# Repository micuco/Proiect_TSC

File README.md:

# Proiect_TSC
InkTime este un smartwatch low-cost, open-source, bazat pe microcontroller-ul nRF52840. Proiectul acopera intreg procesul de dezvoltare hardware, de la schema electrica pana la integrarea mecanica intr-o carcasa.

Sistemul este compus din urmatoarele blocuri principale: MCU nRF52840, Power Management (LiPo Charger + DC/DC), IMU, E-paper Display + Driver, Fuel Gauge, USB-C + ESD Protection, Haptic Driver, Butoane, Interfata SWD.

Microcontroller-ul principal gestioneaza: comunicatia BLE, interfata SPI pentru display, I2C pentru senzori (IMU, fuel gauge),USB pentru alimentare si debug.

Sistemul de alimentare include: BQ25180 pentru incarcarea bateriei LiPo, RT6160 pentru conversie DC/DC, multiple condensatoare de decuplare (100nF, 1uF, 4.7uF). Traseele de alimentare sunt dimensionate conform cerintelor (min 0.3mm).

IMU (BMA421): conectat pe I2C (SDA, SCL), semnale de intrerupere: INT1, INT2, utilizat pentru detectarea miscarii si gesturilor.

E-Paper Display: conectare prin SPI (MOSI, SCK, CS, DC, RST), driver dedicat pentru generarea tensiunilor necesare (boost circuit).

Fuel Gauge: monitorizeaza nivelul bateriei, conectat pe I2C, pin ALERT pentru notificari.

Haptic Driver: DRV2605 pentru control vibratii, control prin I2C, semnal enable din MCU.

USB-C: folosit pentru alimentare si comunicatie, protejat cu circuit ESD dedicat.

Butoane: 3 butoane, conectate la GPIO cu rezistente pull-up/pull-down.

Pin Mapping (nRF52840):

| Functie       | Pin     |
| ------------- | ------- |
| I2C SDA       | P0.xx   |
| I2C SCL       | P0.xx   |
| SPI MOSI      | P0.xx   |
| SPI SCK       | P0.xx   |
| EPD CS/DC/RST | GPIO    |
| IMU INT       | GPIO    |
| SWDIO         | dedicat |
| SWDCLK        | dedicat |

Design Decisions: folosirea e-paper pentru consum redus, integrarea fuel gauge pentru autonomie, antena externa pozitionata la marginea PCB-ului, separarea clara a planurilor de masa.

DRC & ERC: verificari efectuate, respectate regulile de routare, fara unghiuri de 90, condensatoare de decuplare aproape de IC-uri.

PCB Design: PCB 2 layer (TOP + BOTTOM), plan de masa pe ambele layere, via stitching pentru GND, componente plasate pe TOP, trasee: power: ≥ 0.3mm, semnal: ≥ 0.15mm, antena: plasata la marginea PCB, fara plan de masa sub ea.

Modelul 3D include: PCB complet cu componente, baterie LiPo (modelata conform datasheet), display e-paper, carcasa smartwatch.

Integrarea presupune: alinierea butoanelor cu carcasa, pozitionarea corecta a USB-C, fixarea bateriei pe test pads, verificarea spatiului intern si a interferentelor..

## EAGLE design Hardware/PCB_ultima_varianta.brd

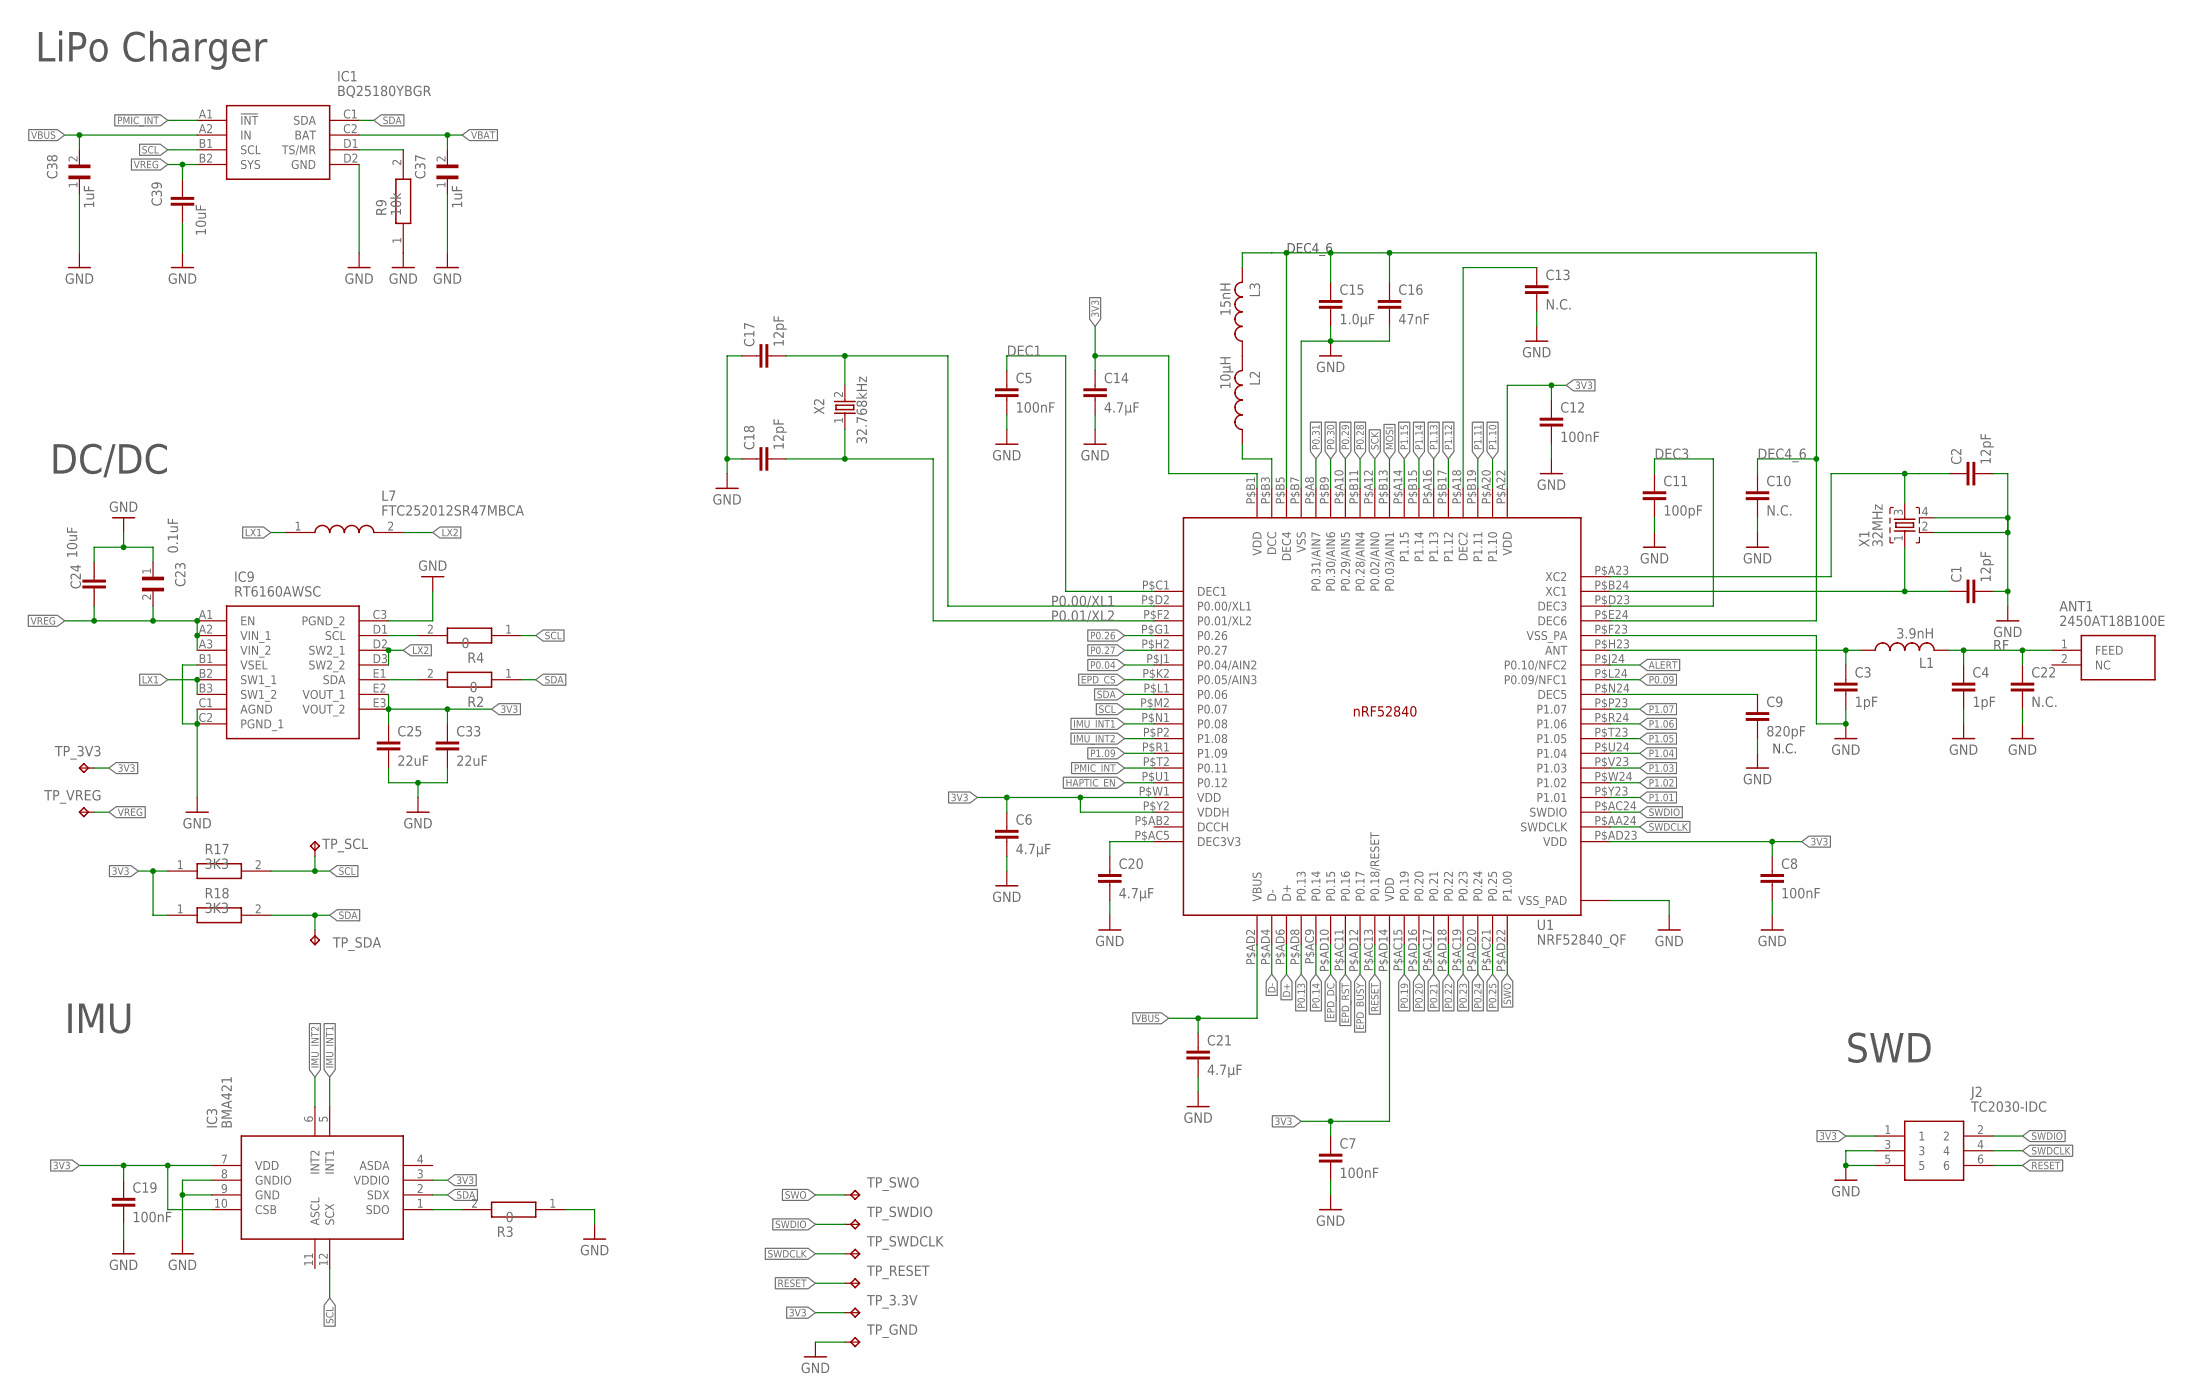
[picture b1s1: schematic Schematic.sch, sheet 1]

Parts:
ANT1: 2450AT18B100E; 2450AT18B100E_ANTC3216X140N
C1, C2, C17, C18: 12pF; NORDIC_NRF_3_RESC0201_L
C3, C4: 1pF; NORDIC_NRF_3_RESC0201_L
C5, C7, C8, C12, C19: 100nF; NORDIC_NRF_3_RESC0201_L
C6, C14, C20, C21: 4.7µF; NORDIC_NRF_3_RESC0201_L
C9: 820pF; NORDIC_NRF_3_RESC0201_L
C10, C13, C22: N.C.; NORDIC_NRF_3_RESC0201_L
C11: 100pF; NORDIC_NRF_3_RESC0201_L
C15: 1.0µF; NORDIC_NRF_3_RESC0201_L
C16: 47nF; NORDIC_NRF_3_RESC0201_L
C23: 0.1uF; GRM011R60J152KE01L_2_CAPC0201X13N
C24, C39: 10uF; NORDIC_NRF_3_RESC0201_L
C25, C33: 22uF; NORDIC_NRF_3_RESC0201_L
C37, C38: 1uF; GRM011R60J152KE01L_2_CAPC0201X13N
IC1: BQ25180YBGR; BQ25180YBGR_BGA8C40P2X4_100X155X50
IC3: BMA421; BMA423_BMA423
IC9: RT6160AWSC; RT6160AWSC_BGA15C40P3X5_140X230X60
J2: TC2030-IDC; TC2030-IDC_TC2030IDC
L1: 3.9nH; NORDIC_NRF_2_RESC0402_L
L2: 10µH; NORDIC_NRF_2_RESC0402_L
L3: 15nH; NORDIC_NRF_2_RESC0402_L
L7: FTC252012SR47MBCA; MLP2016SR47MT0S1_INDC2016X100N
R2, R3, R4: 0; CPF0201D7K68C1_0201
R9: 10k; CPF0201D7K68C1_0201
R17, R18: 3K3; CPF0201D7K68C1_0201
TP_3.3V, TP_3V3: HECTOR_WATCH_1_TPTP20R; HECTOR_WATCH_1_TP20R
TP_GND: HECTOR_WATCH_1_TPTP20R; HECTOR_WATCH_1_TP20R
TP_RESET: HECTOR_WATCH_1_TPTP20R; HECTOR_WATCH_1_TP20R
TP_SCL: HECTOR_WATCH_1_TPTP20R; HECTOR_WATCH_1_TP20R
TP_SDA: HECTOR_WATCH_1_TPTP20R; HECTOR_WATCH_1_TP20R
TP_SWDCLK: HECTOR_WATCH_1_TPTP20R; HECTOR_WATCH_1_TP20R
TP_SWDIO: HECTOR_WATCH_1_TPTP20R; HECTOR_WATCH_1_TP20R
TP_SWO: HECTOR_WATCH_1_TPTP20R; HECTOR_WATCH_1_TP20R
TP_VREG: HECTOR_WATCH_1_TPTP20R; HECTOR_WATCH_1_TP20R
U1: NRF52840_QF; NORDIC_NRF_4_AQFN50P700X700X85_HS-74N
X1: 32MHz; NORDIC_NRF_BT-XTAL_2016_N
X2: 32.768kHz; NORDIC_NRF_1_XTAL_3215_N

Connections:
3V3: C6.1, C7.1, C8.1, C12.1, C14.1, C19.1, C25.1, C33.1, IC3.3 (VDDIO), IC3.7 (VDD), IC3.10 (CSB), IC9.E2 (VOUT_1), IC9.E3 (VOUT_2), J2.1, R17.1, R18.1, TP_3.3V.TP, TP_3V3.TP, U1.P$A22 (VDD), U1.P$AD14 (VDD), U1.P$AD23 (VDD), U1.P$B1 (VDD), U1.P$W1 (VDD), U1.P$Y2 (VDDH); also elsewhere on the board
ALERT: U1.P$J24 (P0.10/NFC2); also elsewhere on the board
D+: U1.P$AD6 (D+); also elsewhere on the board
D-: U1.P$AD4 (D-); also elsewhere on the board
DEC1: C5.1, U1.P$C1 (DEC1)
DEC3: C11.1, U1.P$D23 (DEC3)
DEC4_6: C10.1, C15.1, C16.1, L3.2, U1.P$B5 (DEC4), U1.P$E24 (DEC6)
EPD_BUSY: U1.P$AD12 (P0.17); also elsewhere on the board
EPD_CS: U1.P$K2 (P0.05/AIN3); also elsewhere on the board
EPD_DC: U1.P$AD10 (P0.15); also elsewhere on the board
EPD_RST: U1.P$AC11 (P0.16); also elsewhere on the board
GND: C1.2, C2.2, C3.2, C4.2, C5.2, C6.2, C7.2, C8.2, C9.2, C10.2, C11.2, C12.2, C13.2, C14.2, C15.2, C16.2, C17.1, C18.1, C19.2, C20.2, C21.2, C22.2, C23.1, C24.2, C25.2, C33.2, C37.1, C38.1, C39.2, IC1.D2 (GND), IC3.8 (GNDIO), IC3.9 (GND), IC9.B1 (VSEL), IC9.C1 (AGND), IC9.C2 (PGND_1), IC9.C3 (PGND_2), J2.3, J2.5, R3.1, R9.1, TP_GND.TP, U1.P$74 (VSS_PAD), U1.P$75 (VSS_PAD), U1.P$76 (VSS_PAD), U1.P$77 (VSS_PAD), U1.P$78 (VSS_PAD), U1.P$79 (VSS_PAD), U1.P$80 (VSS_PAD), U1.P$81 (VSS_PAD), U1.P$82 (VSS_PAD), U1.P$83 (VSS_PAD), U1.P$84 (VSS_PAD), U1.P$85 (VSS_PAD), U1.P$86 (VSS_PAD), U1.P$87 (VSS_PAD), U1.P$88 (VSS_PAD), U1.P$89 (VSS_PAD), U1.P$90 (VSS_PAD), U1.P$B7 (VSS), U1.P$F23 (VSS_PA), X1.2, X1.4; also elsewhere on the board
HAPTIC_EN: U1.P$U1 (P0.12); also elsewhere on the board
IMU_INT1: IC3.5 (INT1), U1.P$N1 (P0.08)
IMU_INT2: IC3.6 (INT2), U1.P$P2 (P1.08)
LX1: IC9.B2 (SW1_1), IC9.B3 (SW1_2), L7.1
LX2: IC9.D2 (SW2_1), IC9.D3 (SW2_2), L7.2
MOSI: U1.P$B13 (P0.03/AIN1); also elsewhere on the board
unnamed: IC1.D1 (TS/MR), R9.2
unnamed: IC3.1 (SDO), R3.2
unnamed: C13.1, U1.P$A18 (DEC2)
unnamed: IC9.D1 (SCL), R4.2
unnamed: IC9.E1 (SDA), R2.2
unnamed: C9.1, U1.P$N24 (DEC5)
unnamed: C20.1, U1.P$AC5 (DEC3V3)
unnamed: L2.2, L3.1
unnamed: L2.1, U1.P$B3 (DCC)
unnamed: C3.1, L1.1, U1.P$H23 (ANT)
unnamed: C1.1, U1.P$B24 (XC1), X1.1
unnamed: C2.1, U1.P$A23 (XC2), X1.3
P0.00/XL1: C17.2, U1.P$D2 (P0.00/XL1), X2.2
P0.01/XL2: C18.2, U1.P$F2 (P0.01/XL2), X2.1
P0.04: U1.P$J1 (P0.04/AIN2)
P0.09: U1.P$L24 (P0.09/NFC1)
P0.13: U1.P$AD8 (P0.13); also elsewhere on the board
P0.14: U1.P$AC9 (P0.14); also elsewhere on the board
P0.19: U1.P$AC15 (P0.19)
P0.20: U1.P$AD16 (P0.20)
P0.21: U1.P$AC17 (P0.21)
P0.22: U1.P$AD18 (P0.22)
P0.23: U1.P$AC19 (P0.23)
P0.24: U1.P$AD20 (P0.24)
P0.25: U1.P$AC21 (P0.25)
P0.26: U1.P$G1 (P0.26)
P0.27: U1.P$H2 (P0.27)
P0.28: U1.P$B11 (P0.28/AIN4)
P0.29: U1.P$A10 (P0.29/AIN5)
P0.30: U1.P$B9 (P0.30/AIN6)
P0.31: U1.P$A8 (P0.31/AIN7)
P1.01: U1.P$Y23 (P1.01); also elsewhere on the board
P1.02: U1.P$W24 (P1.02); also elsewhere on the board
P1.03: U1.P$V23 (P1.03)
P1.04: U1.P$U24 (P1.04)
P1.05: U1.P$T23 (P1.05)
P1.06: U1.P$R24 (P1.06)
P1.07: U1.P$P23 (P1.07)
P1.09: U1.P$R1 (P1.09)
P1.10: U1.P$A20 (P1.10)
P1.11: U1.P$B19 (P1.11)
P1.12: U1.P$B17 (P1.12)
P1.13: U1.P$A16 (P1.13)
P1.14: U1.P$B15 (P1.14)
P1.15: U1.P$A14 (P1.15)
PMIC_INT: IC1.A1 (!INT), U1.P$T2 (P0.11)
RESET: J2.6, TP_RESET.TP, U1.P$AC13 (P0.18/RESET)
RF: ANT1.1 (FEED), C4.1, C22.1, L1.2
SCK: U1.P$A12 (P0.02/AIN0); also elsewhere on the board
SCL: IC1.B1 (SCL), IC3.12 (SCX), R4.1, R17.2, TP_SCL.TP, U1.P$M2 (P0.07); also elsewhere on the board
SDA: IC1.C1 (SDA), IC3.2 (SDX), R2.1, R18.2, TP_SDA.TP, U1.P$L1 (P0.06); also elsewhere on the board
SWDCLK: J2.4, TP_SWDCLK.TP, U1.P$AA24 (SWDCLK)
SWDIO: J2.2, TP_SWDIO.TP, U1.P$AC24 (SWDIO)
SWO: TP_SWO.TP, U1.P$AD22 (P1.00)
VBAT: C37.2, IC1.C2 (BAT); also elsewhere on the board
VBUS: C21.1, C38.2, IC1.A2 (IN), U1.P$AD2 (VBUS); also elsewhere on the board
VREG: C23.2, C24.1, C39.1, IC1.B2 (SYS), IC9.A1 (EN), IC9.A2 (VIN_1), IC9.A3 (VIN_2), TP_VREG.TP

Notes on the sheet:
LiPo Charger
DC/DC
IMU
SWD
N.C.
DEC4_6

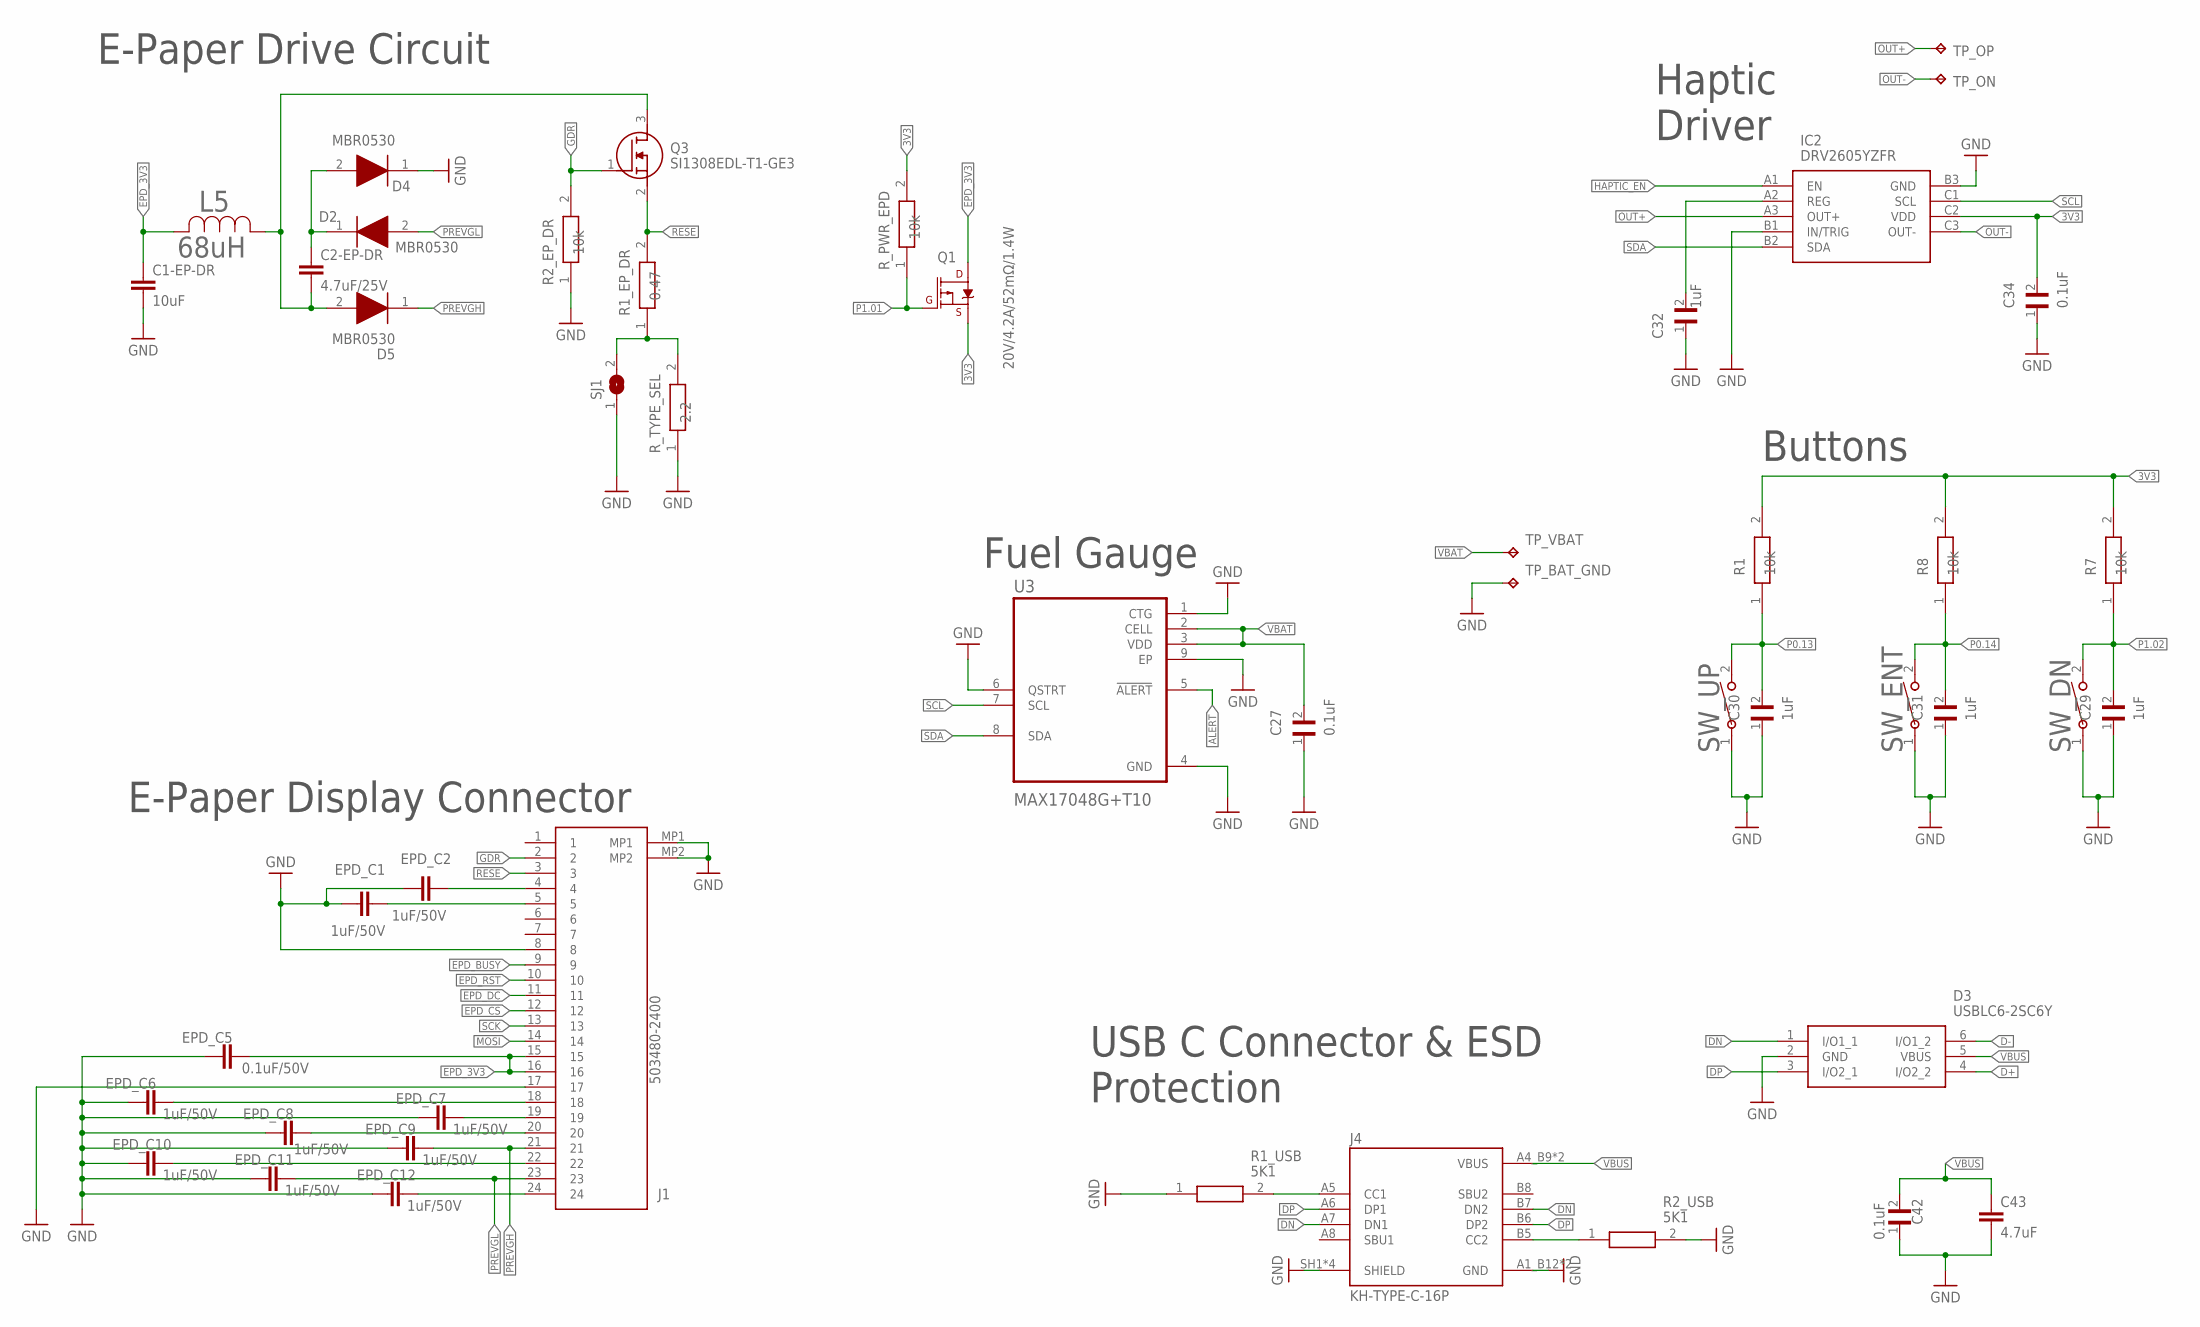
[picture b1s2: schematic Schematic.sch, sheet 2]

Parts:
C1-EP-DR: 10uF; NORDIC_NRF_3_RESC0201_L
C2-EP-DR: 4.7uF/25V; NORDIC_NRF_3_RESC0201_L
C27, C34, C42: 0.1uF; GRM011R60J152KE01L_2_CAPC0201X13N
C29, C30, C31, C32: 1uF; GRM011R60J152KE01L_2_CAPC0201X13N
C43: 4.7uF; NORDIC_NRF_3_RESC0201_L
D2, D4, D5: MBR0530; ESP32_C6_LIBRARY_5_SOD3716X135N
D3: USBLC6-2SC6Y; ESP32_C6_LIBRARY_3_SOT95P280X145-6N
EPD_C1, EPD_C2, EPD_C6, EPD_C7, EPD_C8, EPD_C9, EPD_C10, EPD_C11, EPD_C12: 1uF/50V; NORDIC_NRF_3_RESC0201_L
EPD_C5: 0.1uF/50V; NORDIC_NRF_3_RESC0201_L
IC2: DRV2605YZFR; DRV2605YZFR_BGA9C50P3X3_144X144X62
J1: 503480-2400; 503480-2400_5034802400
J4: KH-TYPE-C-16P; KH-TYPE-C-16P_KINGHELM_KH-TYPE-C-16P
L5: 68uH; ESP32_C6_LIBRARY_2_IND_4828-WE-TPC_WRE
Q1: 20V/4.2A/52mΩ/1.4W; ESP32_C6_LIBRARY_4_ESP32_C6_LIBRARY_4_ESP32_C6_LIBRARY_4_ES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
Q3: SI1308EDL-T1-GE3; ESP32_C6_LIBRARY_6_SOT65P210X110-3N
R1, R7, R8: 10k; CPF0201D7K68C1_0201
R1_EP_DR: 0.47; ERA-1AEB3401C_0201
R1_USB: 5K1; CPF0201D7K68C1_0201
R2_EP_DR: 10k; ERA-1AEB3401C_0201
R2_USB: 5K1; ERA-1AEB3401C_0201
R_PWR_EPD: 10k; CPF0201D7K68C1_0201
R_TYPE_SEL: 2.2; ERA-1AEB3401C_0201
SJ1: ESP32_C6_LIBRARY_7_JUMPER_SJ
SW_DN: 2025-10-22_07-23-44_LIBRARY_EVP-AKE31ASW_EVP-AKE3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; 2025-10-22_07-23-44_LIBRARY_SW_EVP-AKE31A_PAN
SW_ENT: 2025-10-22_07-23-44_LIBRARY_EVP-AKE31ASW_EVP-AKE3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; 2025-10-22_07-23-44_LIBRARY_SW_EVP-AKE31A_PAN
SW_UP: 2025-10-22_07-23-44_LIBRARY_EVP-AKE31ASW_EVP-AKE3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; 2025-10-22_07-23-44_LIBRARY_SW_EVP-AKE31A_PAN
TP_BAT_GND: HECTOR_WATCH_1_TPTP20R; HECTOR_WATCH_1_TP20R
TP_ON: HECTOR_WATCH_1_TPTP20R; HECTOR_WATCH_1_TP20R
TP_OP: HECTOR_WATCH_1_TPTP20R; HECTOR_WATCH_1_TP20R
TP_VBAT: HECTOR_WATCH_1_TPTP20R; HECTOR_WATCH_1_TP20R
U3: MAX17048G+T10; ESP32_C6_LIBRARY_SON50P200X200X80-9N

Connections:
3V3: C34.2, IC2.C2 (VDD), Q1.2 (S), R1.2, R7.2, R8.2, R_PWR_EPD.2; also elsewhere on the board
ALERT: U3.5 (!ALERT); also elsewhere on the board
D+: D3.4 (I/O2_2); also elsewhere on the board
D-: D3.6 (I/O1_2); also elsewhere on the board
DN: D3.1 (I/O1_1), J4.A7 (DN1), J4.B7 (DN2)
DP: D3.3 (I/O2_1), J4.A6 (DP1), J4.B6 (DP2)
EPD_3V3: C1-EP-DR.1, EPD_C5.2, J1.15, J1.16, L5.2, Q1.3 (D)
EPD_BUSY: J1.9; also elsewhere on the board
EPD_CS: J1.12; also elsewhere on the board
EPD_DC: J1.11; also elsewhere on the board
EPD_RST: J1.10; also elsewhere on the board
GDR: J1.2, Q3.1 (G), R2_EP_DR.2
GND: C1-EP-DR.2, C27.1, C29.1, C30.1, C31.1, C32.1, C34.1, C42.1, C43.2, D3.2 (GND), D4.1 (K), EPD_C1.1, EPD_C2.1, EPD_C5.1, EPD_C6.1, EPD_C7.1, EPD_C8.1, EPD_C9.1, EPD_C10.1, EPD_C11.1, EPD_C12.1, IC2.B1 (IN/TRIG), IC2.B3 (GND), J1.8, J1.17, J1.MP1, J1.MP2, J4.A1_B12 (GND), J4.A12_B1 (GND), J4.SH1 (SHIELD), J4.SH2 (SHIELD), J4.SH3 (SHIELD), J4.SH4 (SHIELD), R1_USB.1, R2_EP_DR.1, R2_USB.2, R_TYPE_SEL.1, SJ1.1, SW_DN.1, SW_ENT.1, SW_UP.1, TP_BAT_GND.TP, U3.1 (CTG), U3.4 (GND), U3.6 (QSTRT), U3.9 (EP); also elsewhere on the board
HAPTIC_EN: IC2.A1 (EN); also elsewhere on the board
MOSI: J1.14; also elsewhere on the board
unnamed: C32.2, IC2.A2 (REG)
unnamed: EPD_C2.2, J1.4
unnamed: C2-EP-DR.2, D5.2 (A), L5.1, Q3.3 (D)
unnamed: C2-EP-DR.1, D2.1 (K), D4.2 (A)
unnamed: R1_EP_DR.1, R_TYPE_SEL.2, SJ1.2
unnamed: EPD_C1.2, J1.5
unnamed: J4.B5 (CC2), R2_USB.1
unnamed: EPD_C6.2, J1.18
unnamed: EPD_C7.2, J1.19
unnamed: EPD_C8.2, J1.20
unnamed: EPD_C10.2, J1.22
unnamed: J4.A5 (CC1), R1_USB.2
unnamed: EPD_C12.2, J1.24
OUT+: IC2.A3 (OUT+), TP_OP.TP
OUT-: IC2.C3 (OUT-), TP_ON.TP
P0.13: C30.2, R1.1, SW_UP.2; also elsewhere on the board
P0.14: C31.2, R8.1, SW_ENT.2; also elsewhere on the board
P1.01: Q1.1 (G), R_PWR_EPD.1; also elsewhere on the board
P1.02: C29.2, R7.1, SW_DN.2; also elsewhere on the board
PREVGH: D5.1 (K), EPD_C9.2, J1.21
PREVGL: D2.2 (A), EPD_C11.2, J1.23
RESE: J1.3, Q3.2 (S), R1_EP_DR.2
SCK: J1.13; also elsewhere on the board
SCL: IC2.C1 (SCL), U3.7 (SCL); also elsewhere on the board
SDA: IC2.B2 (SDA), U3.8 (SDA); also elsewhere on the board
VBAT: C27.2, TP_VBAT.TP, U3.2 (CELL), U3.3 (VDD); also elsewhere on the board
VBUS: C42.2, C43.1, D3.5 (VBUS), J4.A4_B9 (VBUS), J4.A9_B4 (VBUS); also elsewhere on the board

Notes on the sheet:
E-Paper Display Connector
Fuel Gauge
USB C Connector & ESD
Protection
Haptic
Driver
Buttons
E-Paper Drive Circuit

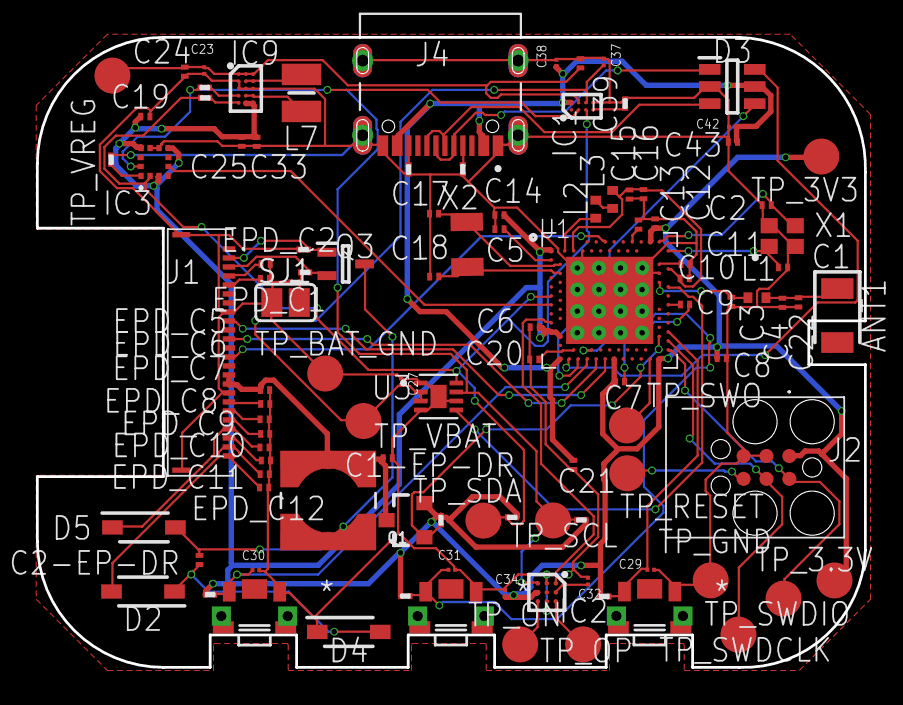
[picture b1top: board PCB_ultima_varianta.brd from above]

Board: 2 copper layers, 46.0 x 35.0 mm, 105 parts (0 on the bottom side), 70 nets.

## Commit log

2026-04-10 mechanical
2026-04-19 varianta finala

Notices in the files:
parts and their libraries:
COPYRIGHT: Copyright (C) 2024 Ultra Librarian. All rights reserved.
COPYRIGHT: Copyright (C) 2025 Ultra Librarian. All rights reserved.
